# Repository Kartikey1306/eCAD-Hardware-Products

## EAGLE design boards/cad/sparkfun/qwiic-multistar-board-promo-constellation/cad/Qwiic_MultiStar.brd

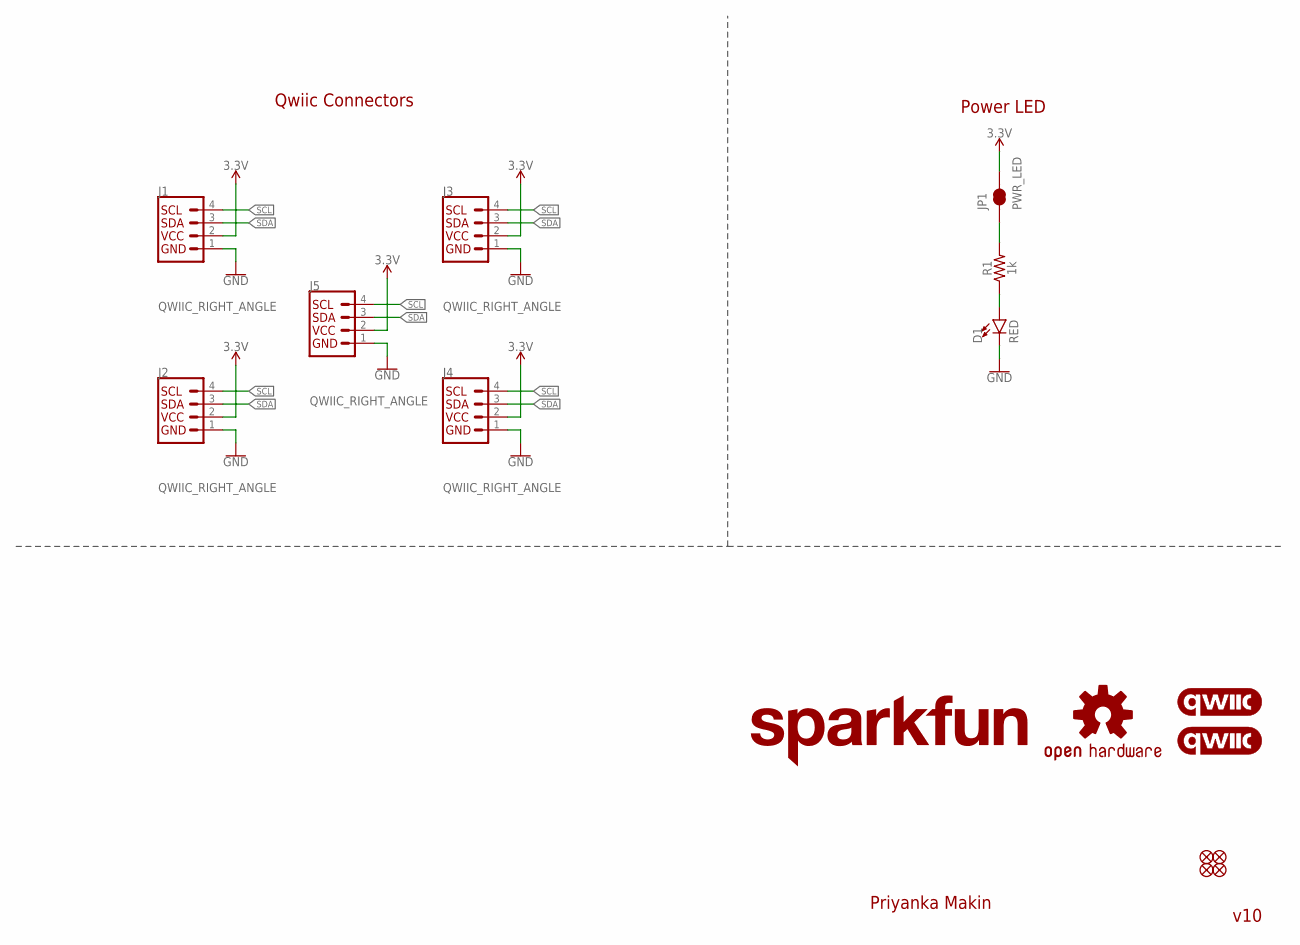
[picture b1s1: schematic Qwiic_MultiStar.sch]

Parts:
D1: RED; LED-0603
FD1, FD2, FD3, FD4: FIDUCIAL1X2; FIDUCIAL-1X2
J1, J2, J3, J4, J5: QWIIC_RIGHT_ANGLE; JST04_1MM_RA
JP1: PWR_LED; SMT-JUMPER_2_NC_TRACE_SILK
LOGO1, LOGO2: QWIIC_LOGO_5MM; QWIIC_5MM
LOGO3: OSHW-LOGOS; OSHW-LOGO-S
LOGO4: SFE_LOGO_NAME.2_INCH; SFE_LOGO_NAME_.2
R1: 1k; 0603

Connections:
3.3V: J1.2, J2.2, J3.2, J4.2, J5.2, JP1.2
GND: D1.C, J1.1, J2.1, J3.1, J4.1, J5.1
unnamed: D1.A, R1.1
unnamed: JP1.1, R1.2
SCL: J1.4, J2.4, J3.4, J4.4, J5.4
SDA: J1.3, J2.3, J3.3, J4.3, J5.3

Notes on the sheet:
Priyanka Makin
v10
Qwiic Connectors
Power LED

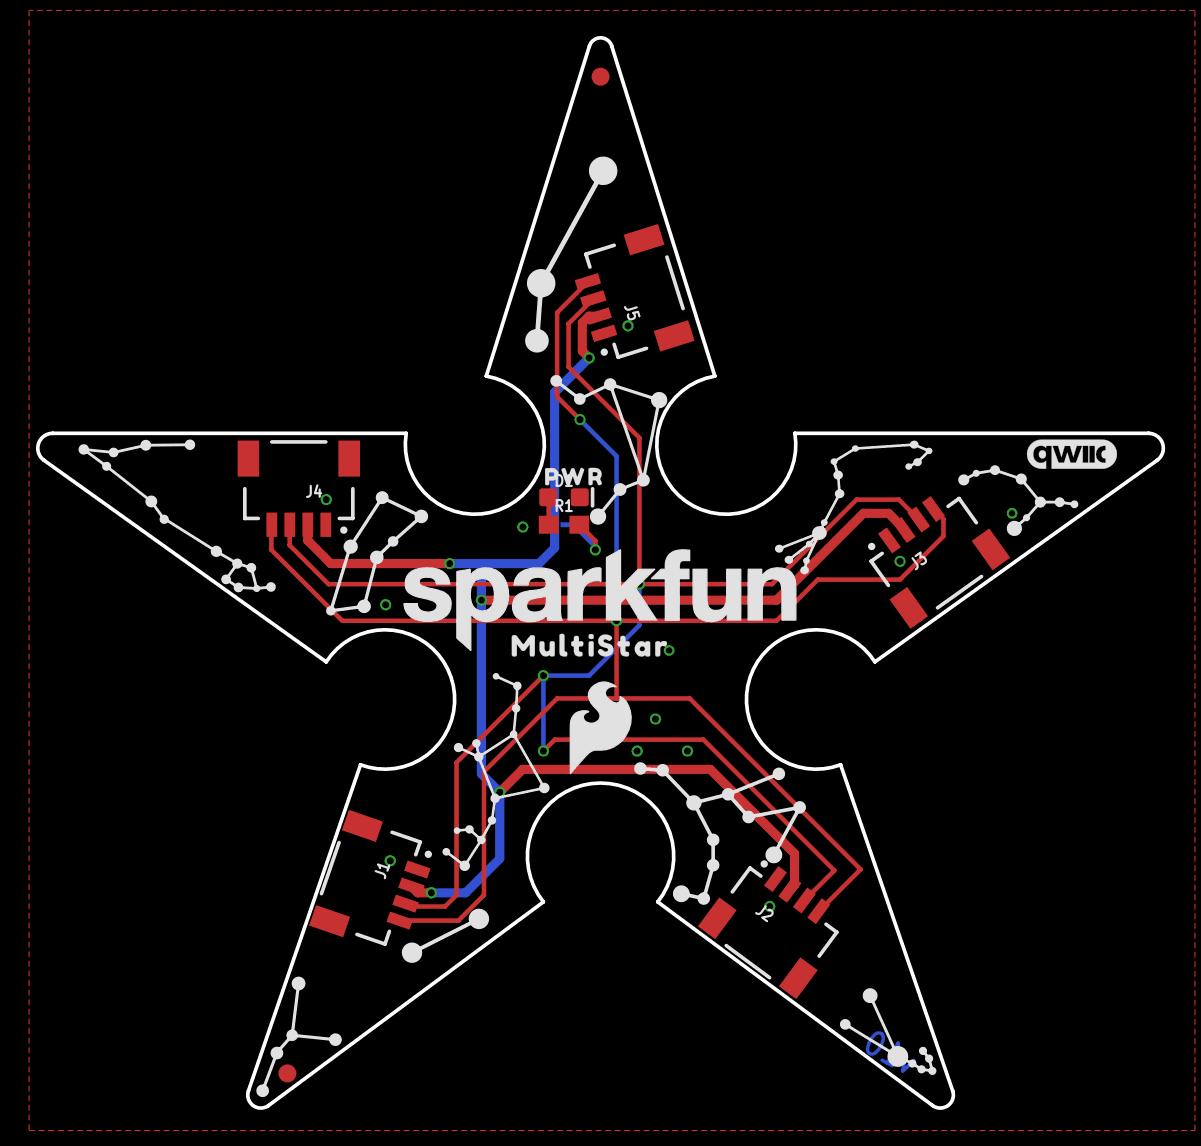
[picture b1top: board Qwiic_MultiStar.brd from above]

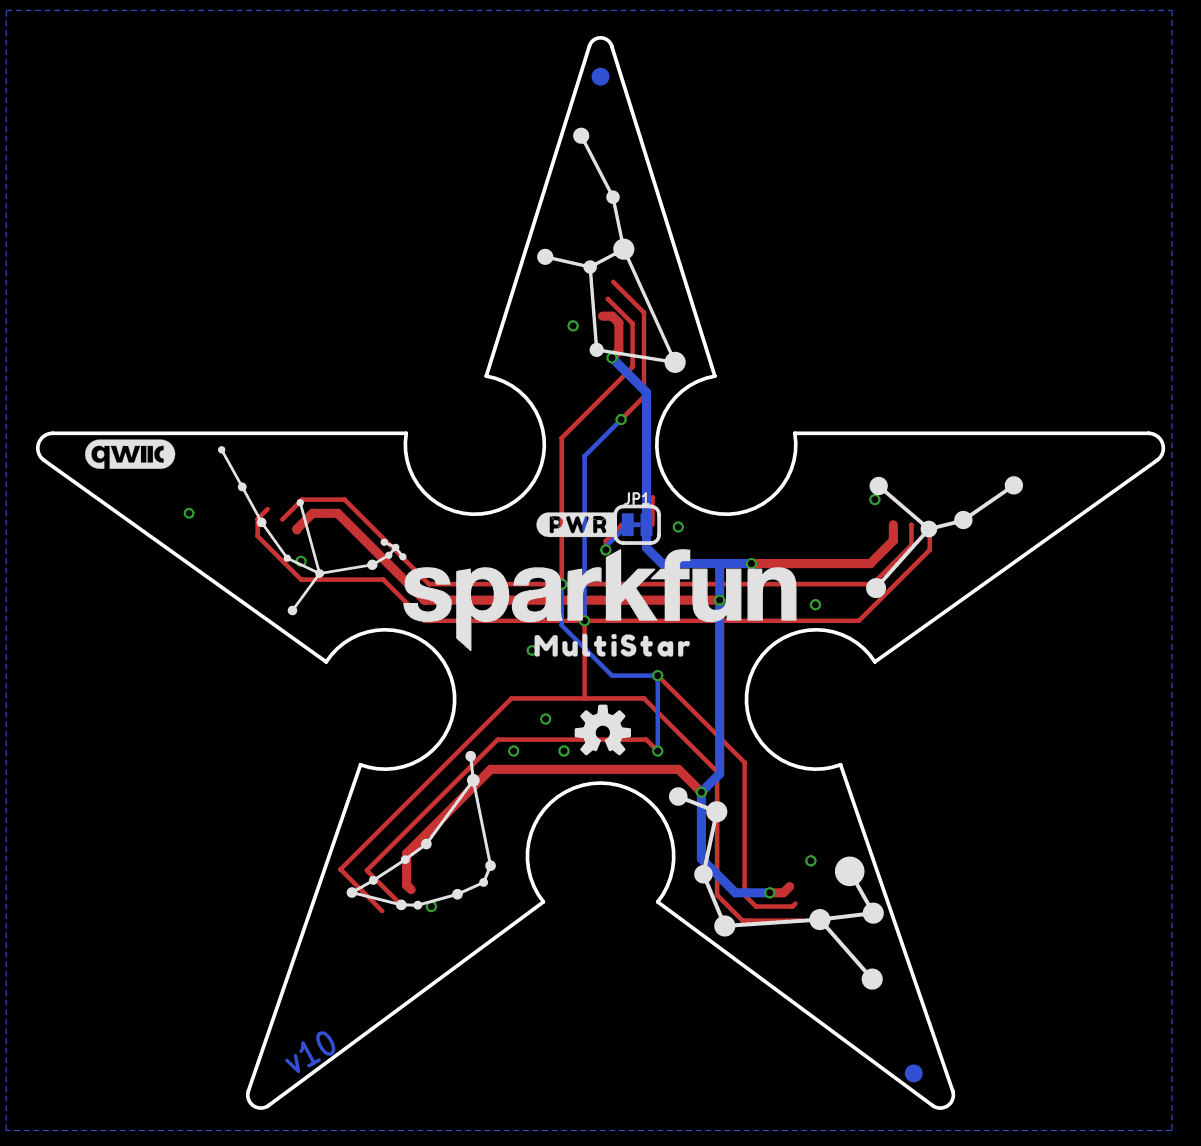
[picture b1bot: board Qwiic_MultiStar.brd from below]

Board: 2 copper layers, 62.5 x 59.5 mm, 23 parts (8 on the bottom side), 6 nets.

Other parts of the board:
FRAME1: FRAME-LETTER; CREATIVE_COMMONS
LOGO5: SFE_LOGO_NAME.2_INCH; SFE_LOGO_NAME_.2
U$2: SFE_LOGO_FLAME_.2
U$3, U$5: MULTISTAR0
U$6: #PWR#0
U$9: PWR0

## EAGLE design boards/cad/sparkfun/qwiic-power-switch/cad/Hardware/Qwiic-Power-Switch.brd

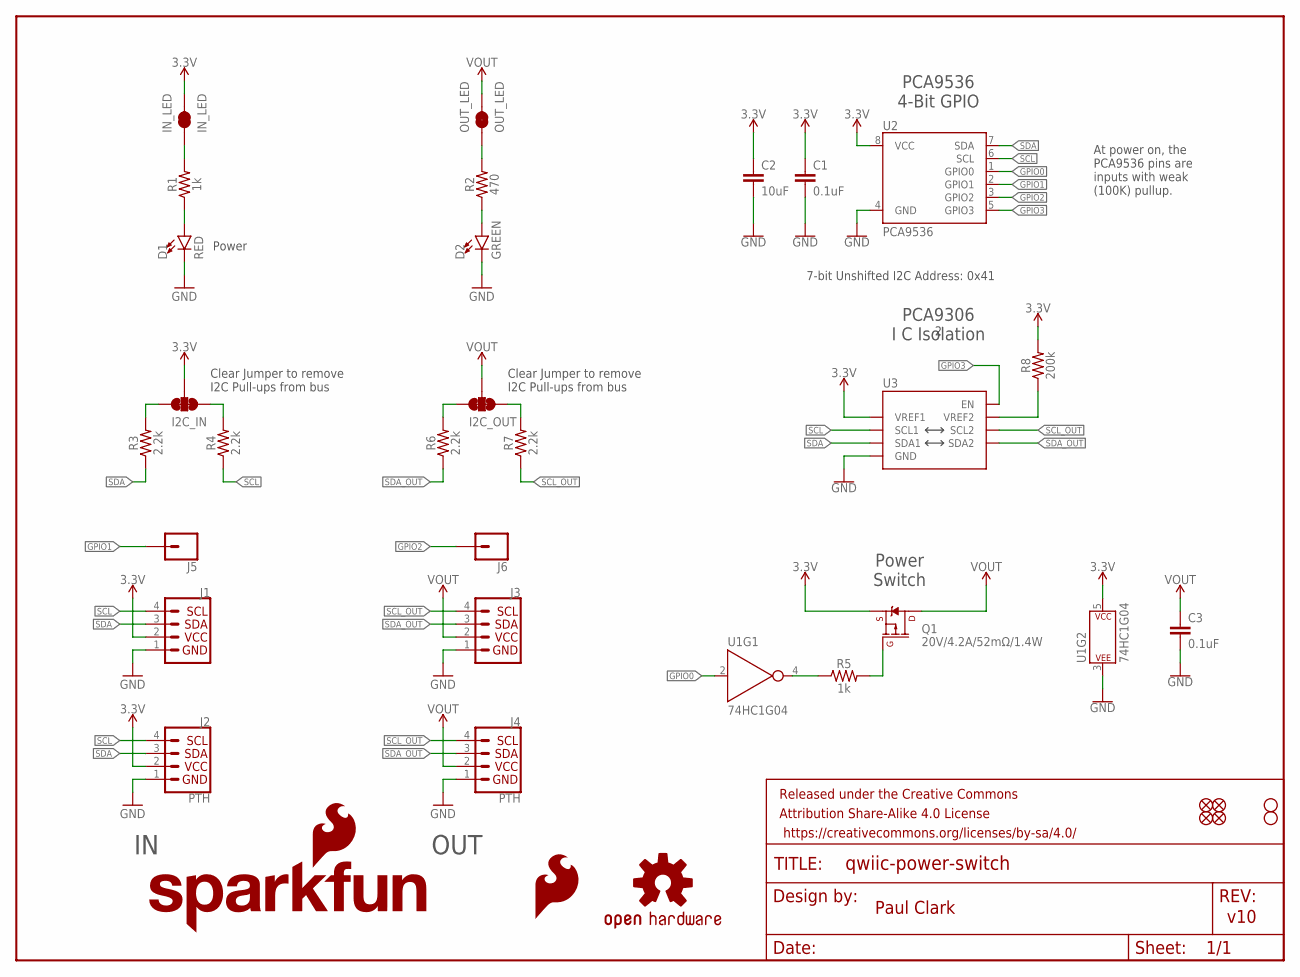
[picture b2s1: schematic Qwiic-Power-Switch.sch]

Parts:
C1, C3: 0.1uF; 0603
C2: 10uF; 0603
D1: RED; LED-0603
D2: GREEN; LED-0603
FRAME1: FRAME-LETTER; CREATIVE_COMMONS
I2C_IN, I2C_OUT: JUMPER-SMT_3_2-NC_TRACE_SILK; SMT-JUMPER_3_2-NC_TRACE_SILK
IN_LED: IN_LED; SMT-JUMPER_2_NC_TRACE_SILK
J1, J3: Qwiic Right Angle; JST04_1MM_RA
J2, J4: PTH; 1X04_NO_SILK
J5, J6: CONN_01PTH_NO_SILK_YES_STOP; 1X01_NO_SILK
JP1, JP2, JP5, JP6: FIDUCIAL1X2; FIDUCIAL-1X2
JP3, JP4: STAND-OFF
LOGO1: OSHW-LOGOMINI; OSHW-LOGO-MINI
LOGO2: SFE_LOGO_FLAME.1_INCH; SFE_LOGO_FLAME_.1
LOGO3: SFE_LOGO_NAME_FLAME.1_INCH; SFE_LOGO_NAME_FLAME_.1
OUT_LED: OUT_LED; SMT-JUMPER_2_NC_TRACE_SILK
Q1: 20V/4.2A/52mΩ/1.4W; SOT23-3
R1, R5: 1k; 0603
R2: 470; 0603
R3, R4, R6, R7: 2.2k; 0603
R8: 200k; 0603
U1: 74HC1G04; SOT353
U2: PCA9536; MSOP8
U3: PCA9306VSSOP_8PIN; VSSOP_8PIN

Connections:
3.3V: C1.1, C2.1, I2C_IN.2, IN_LED.2, J1.2, J2.2, Q1.2 (S), R8.2, U1.5 (P$V+), U2.8 (VCC), U3.P2 (VREF1)
GND: C1.2, C2.2, C3.2, D1.C, D2.C, J1.1, J2.1, J3.1, J4.1, U1.3 (P$V-), U2.4 (GND), U3.P1 (GND)
GPIO0: U1.2 (A), U2.1 (GPIO0)
GPIO1: J5.1, U2.2 (GPIO1)
GPIO2: J6.1, U2.3 (GPIO2)
GPIO3: U2.5 (GPIO3), U3.P8 (EN)
unnamed: I2C_IN.1, R4.2
unnamed: I2C_IN.3, R3.2
unnamed: D1.A, R1.1
unnamed: IN_LED.1, R1.2
unnamed: R5.1, U1.4 (Y)
unnamed: Q1.1 (G), R5.2
unnamed: OUT_LED.1, R2.2
unnamed: I2C_OUT.1, R7.2
unnamed: D2.A, R2.1
unnamed: I2C_OUT.3, R6.2
unnamed: R8.1, U3.P7 (VREF2)
SCL: J1.4, J2.4, R4.1, U2.6 (SCL), U3.P3 (SCL1)
SCL_OUT: J3.4, J4.4, R7.1, U3.P6 (SCL2)
SDA: J1.3, J2.3, R3.1, U2.7 (SDA), U3.P4 (SDA1)
SDA_OUT: J3.3, J4.3, R6.1, U3.P5 (SDA2)
VOUT: C3.1, I2C_OUT.2, J3.2, J4.2, OUT_LED.2, Q1.3 (D)

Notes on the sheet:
Paul Clark
v10
Clear Jumper to remove I2C Pull-ups from bus
Power
7-bit Unshifted I2C Address: 0x41
OUT
At power on, the PCA9536 pins are inputs with weak (100K) pullup.
PCA9536 4-Bit GPIO
PCA9306 I C Isolation
Power Switch

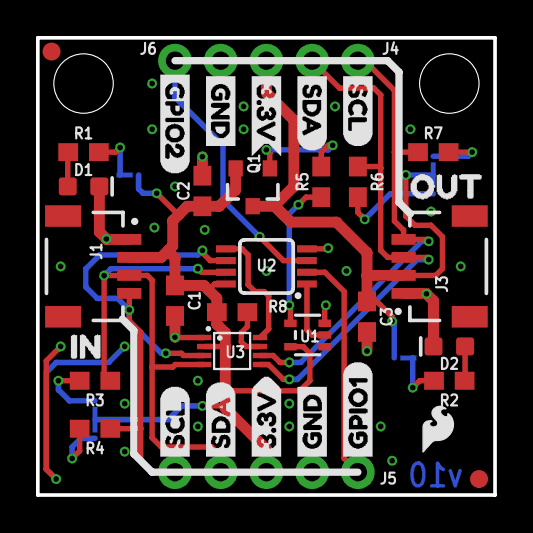
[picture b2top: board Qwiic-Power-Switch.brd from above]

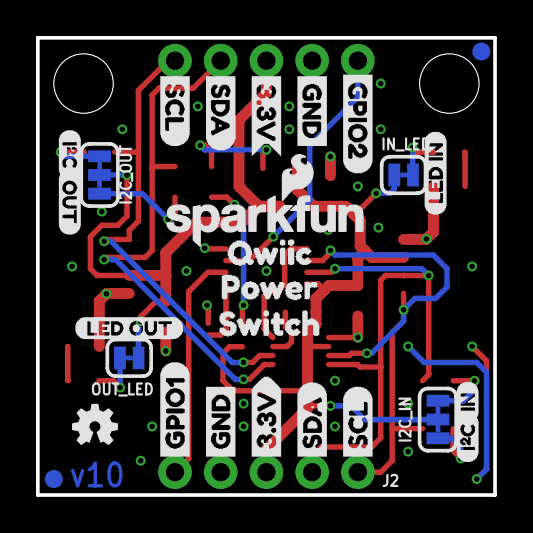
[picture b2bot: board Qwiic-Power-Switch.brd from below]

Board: 2 copper layers, 25.4 x 25.4 mm, 68 parts (28 on the bottom side), 22 nets.

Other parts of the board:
U$1, U$28: IN0
U$3, U$8, U$13, U$22: GND1
U$4, U$7, U$12, U$23: 3#3V0
U$5, U$11, U$15, U$27: SDA8
U$6, U$9, U$17, U$26: SCL9
U$10, U$18: I_SUPER2_C-()-03
U$14, U$31: OUT0
U$16, U$24: GPIO10
U$19: QWIIC0
U$20, U$25: GPIO20
U$29: LED_IN0
U$30: LED_OUT0
U$32: POWER0
U$34: SWITCH0

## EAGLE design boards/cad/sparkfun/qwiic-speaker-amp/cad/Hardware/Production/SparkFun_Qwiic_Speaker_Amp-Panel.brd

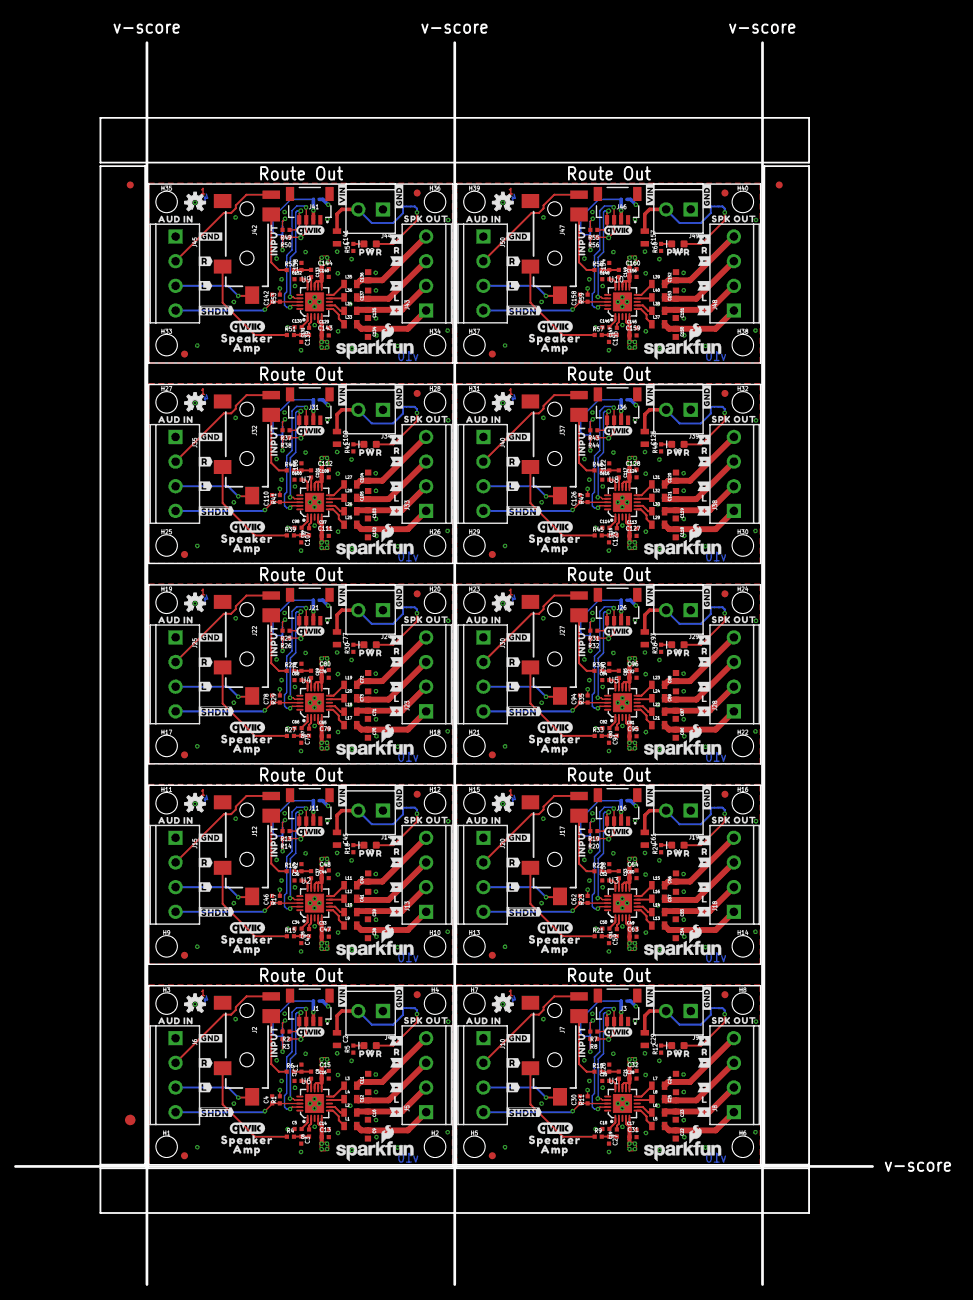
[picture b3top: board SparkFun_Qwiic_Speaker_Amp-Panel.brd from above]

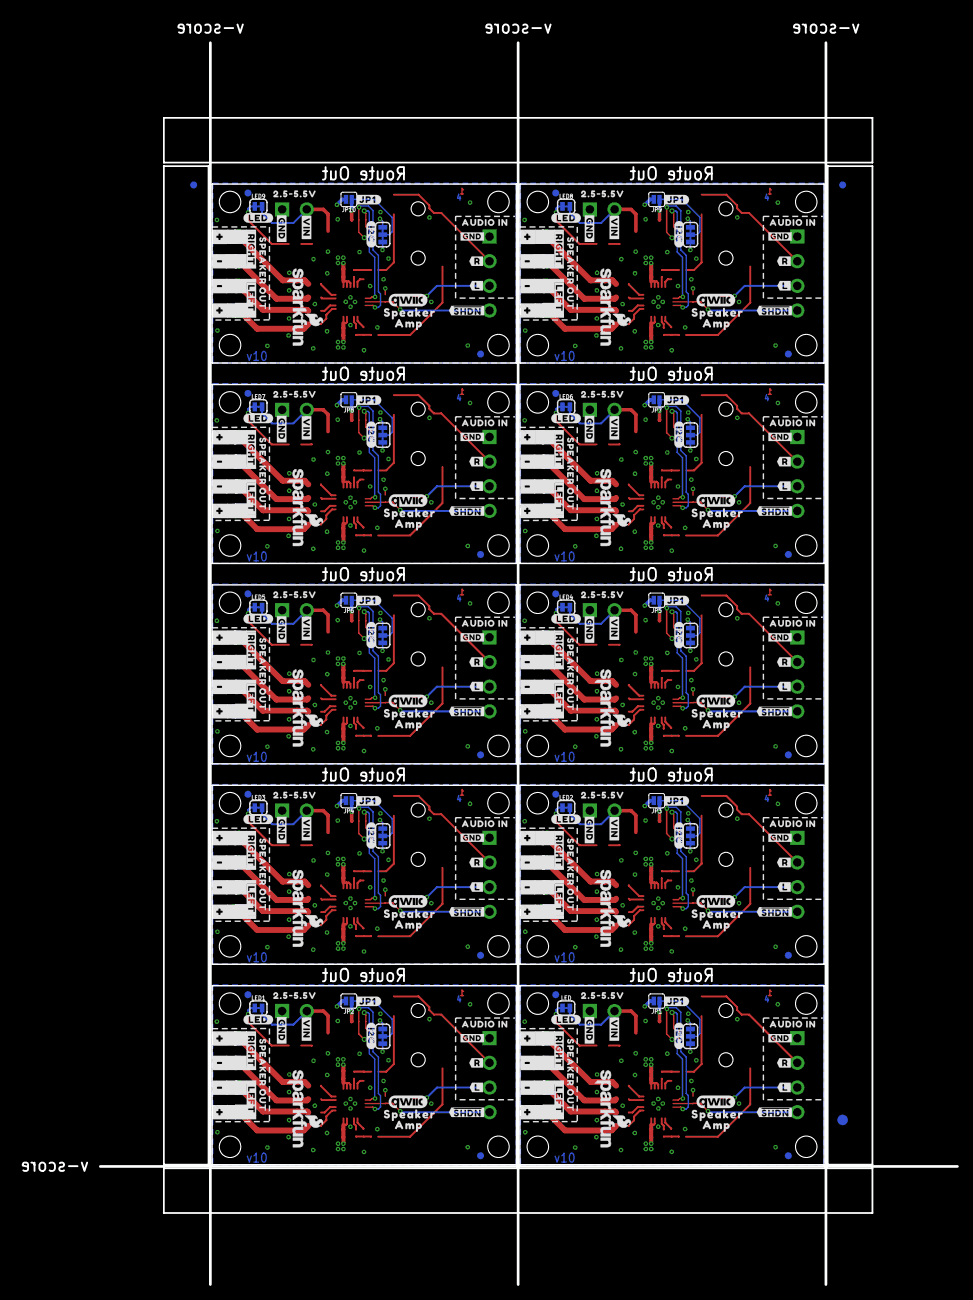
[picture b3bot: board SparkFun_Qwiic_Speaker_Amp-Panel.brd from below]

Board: 4 copper layers, 121.7 x 176.3 mm, 906 parts (273 on the bottom side), 280 nets.

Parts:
C1, C3, C26, C27, C42, C43, C58, C59, C74, C75, C90, C91, C106, C107, C122, C123, C138, C139, C154, C155: 47nF; 0402-TIGHT
C2, C29, C45, C61, C77, C93, C109, C125, C141, C157: 10uF; 0805
C4, C14, C16, C17, C28, C30, C33, C44, C46, C49, C60, C62, C65, C76, C78, C81, C92, C94, C97, C108, C110, C113, C124, C126, C129, C140, C142, C145, C156, C158: 0.1uF; 0402-TIGHT
C5, C6, C7, C8, C13, C15, C18, C19, C20, C21, C31, C32, C34, C35, C36, C37, C47, C48, C50, C51, C52, C53, C63, C64, C66, C67, C68, C69, C79, C80, C82, C83, C84, C85, C95, C96, C98, C99, C100, C101, C111, C112, C114, C115, C116, C117, C127, C128, C130, C131, C132, C133, C143, C144, C146, C147, C148, C149, C159, C160: 1.0uF; 0402-TIGHT
C9, C10, C11, C12, C22, C23, C24, C25, C38, C39, C40, C41, C54, C55, C56, C57, C70, C71, C72, C73, C86, C87, C88, C89, C102, C103, C104, C105, C118, C119, C120, C121, C134, C135, C136, C137, C150, C151, C152, C153: 1nF; 0402
D1, D2, D3, D4, D5, D6, D7, D8, D9, D10: RED; LED-0603
E$1, E$2, E$3, E$4: FIDUCIAL-1X2
E$5, E$6: FIDUCIAL-1.5X3
FD1, FD2, FD3, FD4, FD5, FD6, FD7, FD8, FD9, FD10, FD11, FD12, FD13, FD14, FD15, FD16, FD17, FD18, FD19, FD20, FD21, FD22, FD23, FD24, FD25, FD26, FD27, FD28, FD29, FD30, FD31, FD32, FD33, FD34, FD35, FD36, FD37, FD38, FD39, FD40: FIDUCIAL1X2; FIDUCIAL-1X2
H1, H2, H3, H4, H5, H6, H7, H8, H9, H10, H11, H12, H13, H14, H15, H16, H17, H18, H19, H20, H21, H22, H23, H24, H25, H26, H27, H28, H29, H30, H31, H32, H33, H34, H35, H36, H37, H38, H39, H40: STAND-OFFTIGHT; STAND-OFF-TIGHT
I2C, I2C1, I2C2, I2C3, I2C4, I2C5, I2C6, I2C7, I2C8, I2C9: JUMPER-SMT_3_2-NC_TRACE_SILK; SMT-JUMPER_3_2-NC_TRACE_SILK
J1, J3, J11, J16, J21, J26, J31, J36, J41, J46: QWIIC; JST04_1MM_RA
J2, J7, J12, J17, J22, J27, J32, J37, J42, J47: TRS_INPUT; AUDIO-JACK-3.5MM-SMD
J4, J9, J14, J19, J24, J29, J34, J39, J44, J49: SCREWTERMINAL-3.5MM-2
J5, J8, J13, J18, J23, J28, J33, J38, J43, J48: SCREWTERMINAL-3.5MM-4
J6, J10, J15, J20, J25, J30, J35, J40, J45, J50: SCREW; SCREWTERMINAL-3.5MM-4
JP1, JP2, JP3, JP4, JP5, JP6, JP7, JP8, JP9, JP10: JP1; SMT-JUMPER_2_NO_SILK
L1, L2, L3, L4, L5, L6, L7, L8, L9, L10, L11, L12, L13, L14, L15, L16, L17, L18, L19, L20, L21, L22, L23, L24, L25, L26, L27, L28, L29, L30, L31, L32, L33, L34, L35, L36, L37, L38, L39, L40: 220Ω; 0805
LED, LED1, LED2, LED3, LED4, LED5, LED6, LED7, LED8, LED9: SMT-JUMPER_2_NC_TRACE_SILK
LOGO1, LOGO8, LOGO12, LOGO16, LOGO20, LOGO24, LOGO28, LOGO32, LOGO36, LOGO40: QWIIC_LOGO_4MM; QWIIC_5MM
LOGO2, LOGO5, LOGO9, LOGO13, LOGO17, LOGO21, LOGO25, LOGO29, LOGO33, LOGO37: SFE_LOGO_NAME_FLAME.1_INCH; SFE_LOGO_NAME_FLAME_.1
LOGO3, LOGO6, LOGO10, LOGO14, LOGO18, LOGO22, LOGO26, LOGO30, LOGO34, LOGO38: QWIIC_LOGO_4MM; QWIIC_4MM
LOGO4, LOGO7, LOGO11, LOGO15, LOGO19, LOGO23, LOGO27, LOGO31, LOGO35, LOGO39: OSHW-LOGOS; OSHW-LOGO-S
R1, R11, R17, R23, R29, R35, R41, R47, R53, R59: 100k; 0402-TIGHT
R2, R3, R7, R8, R13, R14, R19, R20, R25, R26, R31, R32, R37, R38, R43, R44, R49, R50, R55, R56: 2.2k; 0402-TIGHT
R4, R6, R9, R10, R15, R16, R21, R22, R27, R28, R33, R34, R39, R40, R45, R46, R51, R52, R57, R58: 100; 0402-TIGHT
R5, R12, R18, R24, R30, R36, R42, R48, R54, R60: 1k; 0402-TIGHT
TP1, TP2, TP3, TP4, TP5, TP6, TP7, TP8, TP9, TP10, TP11, TP12, TP13, TP14, TP15, TP16, TP17, TP18, TP19, TP20: TP_15TH
U1, U2, U3, U4, U5, U6, U7, U8, U9, U10: TPA2016D2; QFN-20-0.5MM
U$1, U$4, U$42, U$45, U$82, U$85, U$122, U$125, U$162, U$165, U$202, U$205, U$242, U$245, U$282, U$285, U$322, U$325, U$362, U$365: SPEAKER0
U$2, U$44, U$84, U$124, U$164, U$204, U$244, U$284, U$324, U$364: #I2C#0
U$3, U$43, U$83, U$123, U$163, U$203, U$243, U$283, U$323, U$363: INPUT0
U$5, U$61, U$101, U$141, U$181, U$221, U$261, U$301, U$341, U$381: PWR26
U$6, U$8, U$41, U$47, U$81, U$87, U$121, U$127, U$161, U$167, U$201, U$207, U$241, U$247, U$281, U$287, U$321, U$327, U$361, U$367: AMP0
U$7, U$46, U$86, U$126, U$166, U$206, U$246, U$286, U$326, U$366: QWIIC_5.5MM
U$9, U$12, U$51, U$54, U$91, U$94, U$131, U$134, U$171, U$174, U$211, U$214, U$251, U$254, U$291, U$294, U$331, U$334, U$371, U$374: ###15
U$10, U$11, U$52, U$53, U$92, U$93, U$132, U$133, U$172, U$173, U$212, U$213, U$252, U$253, U$292, U$293, U$332, U$333, U$372, U$373: ###16
U$13, U$79, U$119, U$159, U$199, U$239, U$279, U$319, U$359, U$399: ##SHDN##3
U$14, U$55, U$95, U$135, U$175, U$215, U$255, U$295, U$335, U$375: R21
U$15, U$59, U$99, U$139, U$179, U$219, U$259, U$299, U$339, U$379: #VIN#24
U$16, U$48, U$88, U$128, U$168, U$208, U$248, U$288, U$328, U$368: L5
U$17, U$49, U$89, U$129, U$169, U$209, U$249, U$289, U$329, U$369: #R#11
U$18, U$66, U$106, U$146, U$186, U$226, U$266, U$306, U$346, U$386: #L#33
U$19, U$50, U$90, U$130, U$170, U$210, U$250, U$290, U$330, U$370: #L#12
U$20, U$25, U$29, U$60, U$63, U$68, U$100, U$103, U$108, U$140, U$143, U$148, U$180, U$183, U$188, U$220, U$223, U$228, U$260, U$263, U$268, U$300, U$303, U$308, U$340, U$343, U$348, U$380, U$383, U$388: #GND#25
U$21, U$56, U$96, U$136, U$176, U$216, U$256, U$296, U$336, U$376: SPK_OUT22
U$22, U$57, U$97, U$137, U$177, U$217, U$257, U$297, U$337, U$377: AUD_IN23
U$23, U$58, U$98, U$138, U$178, U$218, U$258, U$298, U$338, U$378: 2#5#5#5V24
U$24, U$62, U$102, U$142, U$182, U$222, U$262, U$302, U$342, U$382: #LED#27
U$26, U$64, U$104, U$144, U$184, U$224, U$264, U$304, U$344, U$384: #VIN#30
U$27, U$65, U$105, U$145, U$185, U$225, U$265, U$305, U$345, U$385: #GND#31
U$28, U$67, U$107, U$147, U$187, U$227, U$267, U$307, U$347, U$387: #R#34
U$30, U$80, U$120, U$160, U$200, U$240, U$280, U$320, U$360, U$400: SFE_LOGO_NAME_FLAME_.1
U$31, U$32, U$71, U$72, U$111, U$112, U$151, U$152, U$191, U$192, U$231, U$232, U$271, U$272, U$311, U$312, U$351, U$352, U$391, U$392: ###40
U$33, U$69, U$109, U$149, U$189, U$229, U$269, U$309, U$349, U$389: SPEAKER_OUT37
U$34, U$70, U$110, U$150, U$190, U$230, U$270, U$310, U$350, U$390: AUDIO_IN39
U$35, U$36, U$73, U$74, U$113, U$114, U$153, U$154, U$193, U$194, U$233, U$234, U$273, U$274, U$313, U$314, U$353, U$354, U$393, U$394: ###41
U$37, U$75, U$115, U$155, U$195, U$235, U$275, U$315, U$355, U$395: #LEFT#43
U$38, U$76, U$116, U$156, U$196, U$236, U$276, U$316, U$356, U$396: #RIGHT#44
U$39, U$77, U$117, U$157, U$197, U$237, U$277, U$317, U$357, U$397: #JP1#2
U$40, U$78, U$118, U$158, U$198, U$238, U$278, U$318, U$358, U$398: ##SHDN##2

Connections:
3.3V: I2C.2, J1.2, JP1.1
3.3V1: I2C1.2, J3.2, JP2.1
3.3V2: I2C2.2, J11.2, JP3.1
3.3V3: I2C3.2, J16.2, JP4.1
3.3V4: I2C4.2, J21.2, JP5.1
3.3V5: I2C5.2, J26.2, JP6.1
3.3V6: I2C6.2, J31.2, JP7.1
3.3V7: I2C7.2, J36.2, JP8.1
3.3V8: I2C8.2, J41.2, JP9.1
3.3V9: I2C9.2, J46.2, JP10.1
!SDZ!: C4.1, J6.4, R1.1, U6.18
!SDZ!1: C30.1, J10.4, R11.1, U1.18
!SDZ!2: C46.1, J15.4, R17.1, U2.18
!SDZ!3: C62.1, J20.4, R23.1, U3.18
!SDZ!4: C78.1, J25.4, R29.1, U4.18
!SDZ!5: C94.1, J30.4, R35.1, U5.18
!SDZ!6: C110.1, J35.4, R41.1, U7.18
!SDZ!7: C126.1, J40.4, R47.1, U8.18
!SDZ!8: C142.1, J45.4, R53.1, U9.18
!SDZ!9: C158.1, J50.4, R59.1, U10.18
GND: C1.2, C2.2, C3.2, C4.2, C5.1, C7.1, C9.2, C10.2, C11.2, C12.2, C13.2, C14.2, C15.2, C16.2, J1.1, J2.SLEEVE, J4.1, J6.1, R5.1, U6.3, U6.8, U6.PAD
GND1: C17.2, C18.1, C20.1, C22.2, C23.2, C24.2, C25.2, C26.2, C27.2, C28.2, C29.2, C30.2, C31.2, C32.2, J3.1, J7.SLEEVE, J9.1, J10.1, R12.1, U1.3, U1.8, U1.PAD
GND2: C33.2, C34.1, C36.1, C38.2, C39.2, C40.2, C41.2, C42.2, C43.2, C44.2, C45.2, C46.2, C47.2, C48.2, J11.1, J12.SLEEVE, J14.1, J15.1, R18.1, U2.3, U2.8, U2.PAD
GND3: C49.2, C50.1, C52.1, C54.2, C55.2, C56.2, C57.2, C58.2, C59.2, C60.2, C61.2, C62.2, C63.2, C64.2, J16.1, J17.SLEEVE, J19.1, J20.1, R24.1, U3.3, U3.8, U3.PAD
GND4: C65.2, C66.1, C68.1, C70.2, C71.2, C72.2, C73.2, C74.2, C75.2, C76.2, C77.2, C78.2, C79.2, C80.2, J21.1, J22.SLEEVE, J24.1, J25.1, R30.1, U4.3, U4.8, U4.PAD
GND5: C81.2, C82.1, C84.1, C86.2, C87.2, C88.2, C89.2, C90.2, C91.2, C92.2, C93.2, C94.2, C95.2, C96.2, J26.1, J27.SLEEVE, J29.1, J30.1, R36.1, U5.3, U5.8, U5.PAD
GND6: C97.2, C98.1, C100.1, C102.2, C103.2, C104.2, C105.2, C106.2, C107.2, C108.2, C109.2, C110.2, C111.2, C112.2, J31.1, J32.SLEEVE, J34.1, J35.1, R42.1, U7.3, U7.8, U7.PAD
GND7: C113.2, C114.1, C116.1, C118.2, C119.2, C120.2, C121.2, C122.2, C123.2, C124.2, C125.2, C126.2, C127.2, C128.2, J36.1, J37.SLEEVE, J39.1, J40.1, R48.1, U8.3, U8.8, U8.PAD
GND8: C129.2, C130.1, C132.1, C134.2, C135.2, C136.2, C137.2, C138.2, C139.2, C140.2, C141.2, C142.2, C143.2, C144.2, J41.1, J42.SLEEVE, J44.1, J45.1, R54.1, U9.3, U9.8, U9.PAD
GND9: C145.2, C146.1, C148.1, C150.2, C151.2, C152.2, C153.2, C154.2, C155.2, C156.2, C157.2, C158.2, C159.2, C160.2, J46.1, J47.SLEEVE, J49.1, J50.1, R60.1, U10.3, U10.8, U10.PAD
INL: J2.TIP, R4.1
INL1: J7.TIP, R9.1
INL2: J12.TIP, R15.1
INL3: J17.TIP, R21.1
INL4: J22.TIP, R27.1
INL5: J27.TIP, R33.1
INL6: J32.TIP, R39.1
INL7: J37.TIP, R45.1
INL8: J42.TIP, R51.1
INL9: J47.TIP, R57.1
INL_SCRWPN: J2.TSH, J6.3
INL_SCRWPN1: J7.TSH, J10.3
INL_SCRWPN2: J12.TSH, J15.3
INL_SCRWPN3: J17.TSH, J20.3
INL_SCRWPN4: J22.TSH, J25.3
INL_SCRWPN5: J27.TSH, J30.3
INL_SCRWPN6: J32.TSH, J35.3
INL_SCRWPN7: J37.TSH, J40.3
INL_SCRWPN8: J42.TSH, J45.3
INL_SCRWPN9: J47.TSH, J50.3
INR: J2.RING, R6.1
INR1: J7.RING, R10.1
INR2: J12.RING, R16.1
INR3: J17.RING, R22.1
INR4: J22.RING, R28.1
INR5: J27.RING, R34.1
INR6: J32.RING, R40.1
INR7: J37.RING, R46.1
INR8: J42.RING, R52.1
INR9: J47.RING, R58.1
INR_SCRWPN: J2.RSH, J6.2
INR_SCRWPN1: J7.RSH, J10.2
INR_SCRWPN2: J12.RSH, J15.2
INR_SCRWPN3: J17.RSH, J20.2
INR_SCRWPN4: J22.RSH, J25.2
INR_SCRWPN5: J27.RSH, J30.2
INR_SCRWPN6: J32.RSH, J35.2
INR_SCRWPN7: J37.RSH, J40.2
INR_SCRWPN8: J42.RSH, J45.2
INR_SCRWPN9: J47.RSH, J50.2
unnamed: L1.1, U6.6
unnamed: L2.1, U6.7
unnamed: C1.1, C8.1, R6.2
unnamed: D1.C, R5.2
unnamed: C3.1, C6.1, R4.2
unnamed: D1.A, LED.1
unnamed: I2C1.3, R7.2
unnamed: I2C1.1, R8.2
unnamed: C18.2, U1.1
unnamed: C21.2, U1.14
unnamed: C20.2, U1.15
unnamed: C19.2, U1.2
unnamed: L5.1, U1.6
unnamed: L6.1, U1.7
unnamed: L7.1, U1.10
unnamed: I2C.3, R2.2
unnamed: I2C.1, R3.2
unnamed: L3.1, U6.10
unnamed: L4.1, U6.9
unnamed: C8.2, U6.14
unnamed: C5.2, U6.1
unnamed: C6.2, U6.2
unnamed: L8.1, U1.9
unnamed: C21.1, C26.1, R10.2
unnamed: C7.2, U6.15
unnamed: C19.1, C27.1, R9.2
unnamed: D2.C, R12.2
unnamed: D2.A, LED1.1
unnamed: I2C2.3, R13.2
unnamed: I2C2.1, R14.2
unnamed: C34.2, U2.1
unnamed: C37.2, U2.14
unnamed: C36.2, U2.15
unnamed: C35.2, U2.2
unnamed: L9.1, U2.6
unnamed: L10.1, U2.7
unnamed: L11.1, U2.10
unnamed: L12.1, U2.9
unnamed: C37.1, C42.1, R16.2
unnamed: C35.1, C43.1, R15.2
unnamed: D3.C, R18.2
unnamed: D3.A, LED2.1
unnamed: I2C3.3, R19.2
unnamed: I2C3.1, R20.2
unnamed: C50.2, U3.1
unnamed: C53.2, U3.14
unnamed: C52.2, U3.15
unnamed: C51.2, U3.2
unnamed: L13.1, U3.6
unnamed: L14.1, U3.7
unnamed: L15.1, U3.10
unnamed: L16.1, U3.9
unnamed: C53.1, C58.1, R22.2
unnamed: C51.1, C59.1, R21.2
unnamed: D4.C, R24.2
unnamed: D4.A, LED3.1
unnamed: I2C4.3, R25.2
unnamed: I2C4.1, R26.2
unnamed: C66.2, U4.1
unnamed: C69.2, U4.14
unnamed: C68.2, U4.15
unnamed: C67.2, U4.2
unnamed: L17.1, U4.6
unnamed: L18.1, U4.7
unnamed: L19.1, U4.10
unnamed: L20.1, U4.9
unnamed: C69.1, C74.1, R28.2
unnamed: C67.1, C75.1, R27.2
unnamed: D5.C, R30.2
unnamed: D5.A, LED4.1
unnamed: I2C5.3, R31.2
unnamed: I2C5.1, R32.2
unnamed: C82.2, U5.1
unnamed: C85.2, U5.14
unnamed: C84.2, U5.15
unnamed: C83.2, U5.2
unnamed: L21.1, U5.6
unnamed: L22.1, U5.7
unnamed: L23.1, U5.10
unnamed: L24.1, U5.9
unnamed: C85.1, C90.1, R34.2
unnamed: C83.1, C91.1, R33.2
unnamed: D6.C, R36.2
unnamed: D6.A, LED5.1
unnamed: I2C6.3, R37.2
unnamed: I2C6.1, R38.2
unnamed: C98.2, U7.1
unnamed: C101.2, U7.14
unnamed: C100.2, U7.15
unnamed: C99.2, U7.2
unnamed: L25.1, U7.6
unnamed: L26.1, U7.7
unnamed: L27.1, U7.10
unnamed: L28.1, U7.9
unnamed: C101.1, C106.1, R40.2
unnamed: C99.1, C107.1, R39.2
unnamed: D7.C, R42.2
unnamed: D7.A, LED6.1
unnamed: I2C7.3, R43.2
unnamed: I2C7.1, R44.2
unnamed: C114.2, U8.1
unnamed: C117.2, U8.14
unnamed: C116.2, U8.15
unnamed: C115.2, U8.2
unnamed: L29.1, U8.6
unnamed: L30.1, U8.7
unnamed: L31.1, U8.10
unnamed: L32.1, U8.9
unnamed: C117.1, C122.1, R46.2
unnamed: C115.1, C123.1, R45.2
unnamed: D8.C, R48.2
unnamed: D8.A, LED7.1
unnamed: I2C8.3, R49.2
unnamed: I2C8.1, R50.2
unnamed: C130.2, U9.1
unnamed: C133.2, U9.14
unnamed: C132.2, U9.15
unnamed: C131.2, U9.2
unnamed: L33.1, U9.6
unnamed: L34.1, U9.7
unnamed: L35.1, U9.10
unnamed: L36.1, U9.9
unnamed: C133.1, C138.1, R52.2
unnamed: C131.1, C139.1, R51.2
unnamed: D9.C, R54.2
unnamed: D9.A, LED8.1
unnamed: I2C9.3, R55.2
unnamed: I2C9.1, R56.2
unnamed: C146.2, U10.1
unnamed: C149.2, U10.14
unnamed: C148.2, U10.15
unnamed: C147.2, U10.2
unnamed: L37.1, U10.6
unnamed: L38.1, U10.7
unnamed: L39.1, U10.10
unnamed: L40.1, U10.9
unnamed: C149.1, C154.1, R58.2
unnamed: C147.1, C155.1, R57.2
unnamed: D10.C, R60.2
unnamed: D10.A, LED9.1
SCL: J1.4, R2.1, TP1.1, U6.17
SCL1: J3.4, R7.1, TP3.1, U1.17
SCL2: J11.4, R13.1, TP5.1, U2.17
SCL3: J16.4, R19.1, TP7.1, U3.17
SCL4: J21.4, R25.1, TP9.1, U4.17
SCL5: J26.4, R31.1, TP11.1, U5.17
SCL6: J31.4, R37.1, TP13.1, U7.17
SCL7: J36.4, R43.1, TP15.1, U8.17
SCL8: J41.4, R49.1, TP17.1, U9.17
SCL9: J46.4, R55.1, TP19.1, U10.17
SDA: J1.3, R3.1, TP2.1, U6.19
SDA1: J3.3, R8.1, TP4.1, U1.19
SDA2: J11.3, R14.1, TP6.1, U2.19
SDA3: J16.3, R20.1, TP8.1, U3.19
SDA4: J21.3, R26.1, TP10.1, U4.19
SDA5: J26.3, R32.1, TP12.1, U5.19
SDA6: J31.3, R38.1, TP14.1, U7.19
SDA7: J36.3, R44.1, TP16.1, U8.19
SDA8: J41.3, R50.1, TP18.1, U9.19
SDA9: J46.3, R56.1, TP20.1, U10.19
SPK_L_+: C9.1, J5.1, L1.2
SPK_L_+1: C22.1, J8.1, L5.2
SPK_L_+2: C38.1, J13.1, L9.2
SPK_L_+3: C54.1, J18.1, L13.2
SPK_L_+4: C70.1, J23.1, L17.2
SPK_L_+5: C86.1, J28.1, L21.2
SPK_L_+6: C102.1, J33.1, L25.2
SPK_L_+7: C118.1, J38.1, L29.2
SPK_L_+8: C134.1, J43.1, L33.2
SPK_L_+9: C150.1, J48.1, L37.2
SPK_L_-: C10.1, J5.2, L2.2
SPK_L_-1: C23.1, J8.2, L6.2
SPK_L_-2: C39.1, J13.2, L10.2
SPK_L_-3: C55.1, J18.2, L14.2
SPK_L_-4: C71.1, J23.2, L18.2
SPK_L_-5: C87.1, J28.2, L22.2
SPK_L_-6: C103.1, J33.2, L26.2
SPK_L_-7: C119.1, J38.2, L30.2
SPK_L_-8: C135.1, J43.2, L34.2
SPK_L_-9: C151.1, J48.2, L38.2
SPK_R_+: C11.1, J5.4, L3.2
SPK_R_+1: C24.1, J8.4, L7.2
SPK_R_+2: C40.1, J13.4, L11.2
SPK_R_+3: C56.1, J18.4, L15.2
SPK_R_+4: C72.1, J23.4, L19.2
SPK_R_+5: C88.1, J28.4, L23.2
SPK_R_+6: C104.1, J33.4, L27.2
SPK_R_+7: C120.1, J38.4, L31.2
SPK_R_+8: C136.1, J43.4, L35.2
SPK_R_+9: C152.1, J48.4, L39.2
SPK_R_-: C12.1, J5.3, L4.2
SPK_R_-1: C25.1, J8.3, L8.2
SPK_R_-2: C41.1, J13.3, L12.2
SPK_R_-3: C57.1, J18.3, L16.2
SPK_R_-4: C73.1, J23.3, L20.2
SPK_R_-5: C89.1, J28.3, L24.2
SPK_R_-6: C105.1, J33.3, L28.2
SPK_R_-7: C121.1, J38.3, L32.2
SPK_R_-8: C137.1, J43.3, L36.2
SPK_R_-9: C153.1, J48.3, L40.2
VCC: C2.1, C13.1, C14.1, C15.1, C16.1, J4.2, JP1.2, LED.2, R1.2, U6.4, U6.5, U6.11, U6.12, U6.13
VCC1: C17.1, C28.1, C29.1, C31.1, C32.1, J9.2, JP2.2, LED1.2, R11.2, U1.4, U1.5, U1.11, U1.12, U1.13
VCC2: C33.1, C44.1, C45.1, C47.1, C48.1, J14.2, JP3.2, LED2.2, R17.2, U2.4, U2.5, U2.11, U2.12, U2.13
VCC3: C49.1, C60.1, C61.1, C63.1, C64.1, J19.2, JP4.2, LED3.2, R23.2, U3.4, U3.5, U3.11, U3.12, U3.13
VCC4: C65.1, C76.1, C77.1, C79.1, C80.1, J24.2, JP5.2, LED4.2, R29.2, U4.4, U4.5, U4.11, U4.12, U4.13
VCC5: C81.1, C92.1, C93.1, C95.1, C96.1, J29.2, JP6.2, LED5.2, R35.2, U5.4, U5.5, U5.11, U5.12, U5.13
VCC6: C97.1, C108.1, C109.1, C111.1, C112.1, J34.2, JP7.2, LED6.2, R41.2, U7.4, U7.5, U7.11, U7.12, U7.13
VCC7: C113.1, C124.1, C125.1, C127.1, C128.1, J39.2, JP8.2, LED7.2, R47.2, U8.4, U8.5, U8.11, U8.12, U8.13
VCC8: C129.1, C140.1, C141.1, C143.1, C144.1, J44.2, JP9.2, LED8.2, R53.2, U9.4, U9.5, U9.11, U9.12, U9.13
VCC9: C145.1, C156.1, C157.1, C159.1, C160.1, J49.2, JP10.2, LED9.2, R59.2, U10.4, U10.5, U10.11, U10.12, U10.13

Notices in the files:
parts and their libraries:
SparkFun-Connectors: Licensing: Creative Commons ShareAlike 4.0 International - https://creativecommons.org/licenses/by-sa/4.0
SparkFun-Aesthetics: Released under the Creative Commons Attribution Share-Alike 4.0 License
SparkFun-Aesthetics: https://creativecommons.org/licenses/by-sa/4.0
